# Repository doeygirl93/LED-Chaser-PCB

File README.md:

# Chiikawa LED chaser PCD
You can find my journals here: https://stasis.hackclub.com/dashboard/projects/cmnpnfhm200dn01pehbkvc9ek
---
## Description

This is a Blinky Board for stasis! Its very cool and when its powered it has a bunch of Leds "chasing" each other like after one turns on the one before it turns off and it goes through all the Led!

--- 
## Why I made It

I made it because this is one of my First Pcbs! I wanted something easy and people said to do this for the fundamentals. I wanted it to be useful so i made it chiikawa themed cause chiikawa makes me happy!

----
## Pictures

#### Pcb

### Schematic

## 3d Render 

## BOM

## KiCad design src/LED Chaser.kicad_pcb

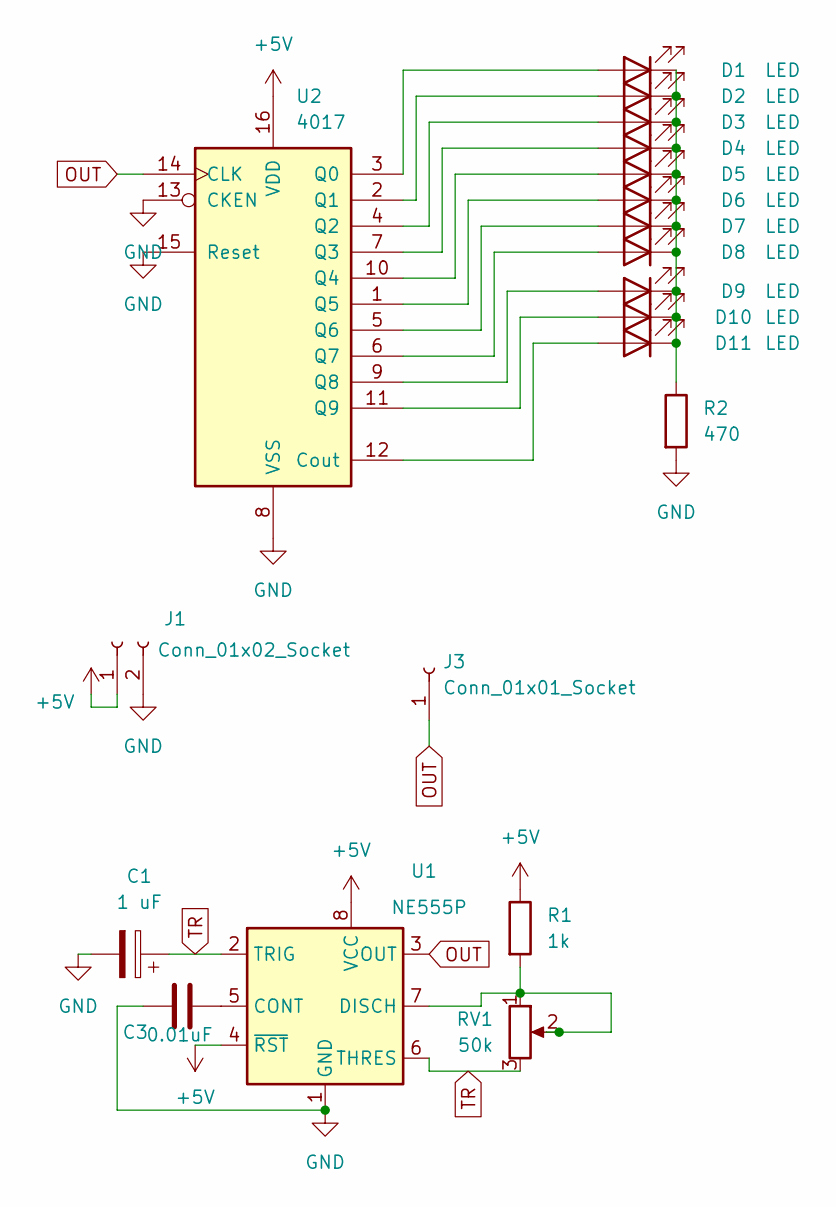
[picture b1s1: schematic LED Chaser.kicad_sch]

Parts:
C1: 1 uF; CP_Radial_D5.0mm_P2.00mm
C3: 0.01uF; CP_Radial_D5.0mm_P2.00mm
D1, D2, D3, D4, D5, D6, D7, D8, D9, D10, D11: LED; LED_D3.0mm
J1: Conn_01x02_Socket; PinHeader_1x02_P2.54mm_Vertical
J3: Conn_01x01_Socket; PinHeader_1x02_P2.54mm_Vertical
R1: 1k; R_Axial_DIN0207_L6.3mm_D2.5mm_P7.62mm_Horizontal
R2: 470; R_Axial_DIN0207_L6.3mm_D2.5mm_P7.62mm_Horizontal
RV1: 50k; Potentiometer_Vishay_T93YA_Vertical
U1: NE555P; DIP-8_W7.62mm
U2: 4017; N16

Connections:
+5V: J1.1, R1.1, U1.4 (~RST), U1.8 (VCC), U2.16 (VDD)
GND: C1.2, C3.1, J1.2, R2.2, U1.1 (GND), U2.8 (VSS), U2.13 (CKEN), U2.15 (Reset)
unnamed: D1.2 (A), U2.3 (Q0)
unnamed: D1.1 (K), D2.1 (K), D3.1 (K), D4.1 (K), D5.1 (K), D6.1 (K), D7.1 (K), D8.1 (K), D9.1 (K), D10.1 (K), D11.1 (K), R2.1
unnamed: D2.2 (A), U2.2 (Q1)
unnamed: D3.2 (A), U2.4 (Q2)
unnamed: D4.2 (A), U2.7 (Q3)
unnamed: D5.2 (A), U2.10 (Q4)
unnamed: D6.2 (A), U2.1 (Q5)
unnamed: D7.2 (A), U2.5 (Q6)
unnamed: D8.2 (A), U2.6 (Q7)
unnamed: D9.2 (A), U2.9 (Q8)
unnamed: D10.2 (A), U2.11 (Q9)
unnamed: D11.2 (A), U2.12 (Cout)
unnamed: C3.2, U1.5 (CONT)
unnamed: R1.2, RV1.1, RV1.2, U1.7 (DISCH)
OUT: J3.1 (Pin_1_1), U1.3 (OUT), U2.14 (CLK)
TR: C1.1, RV1.3, U1.2 (TRIG), U1.6 (THRES)

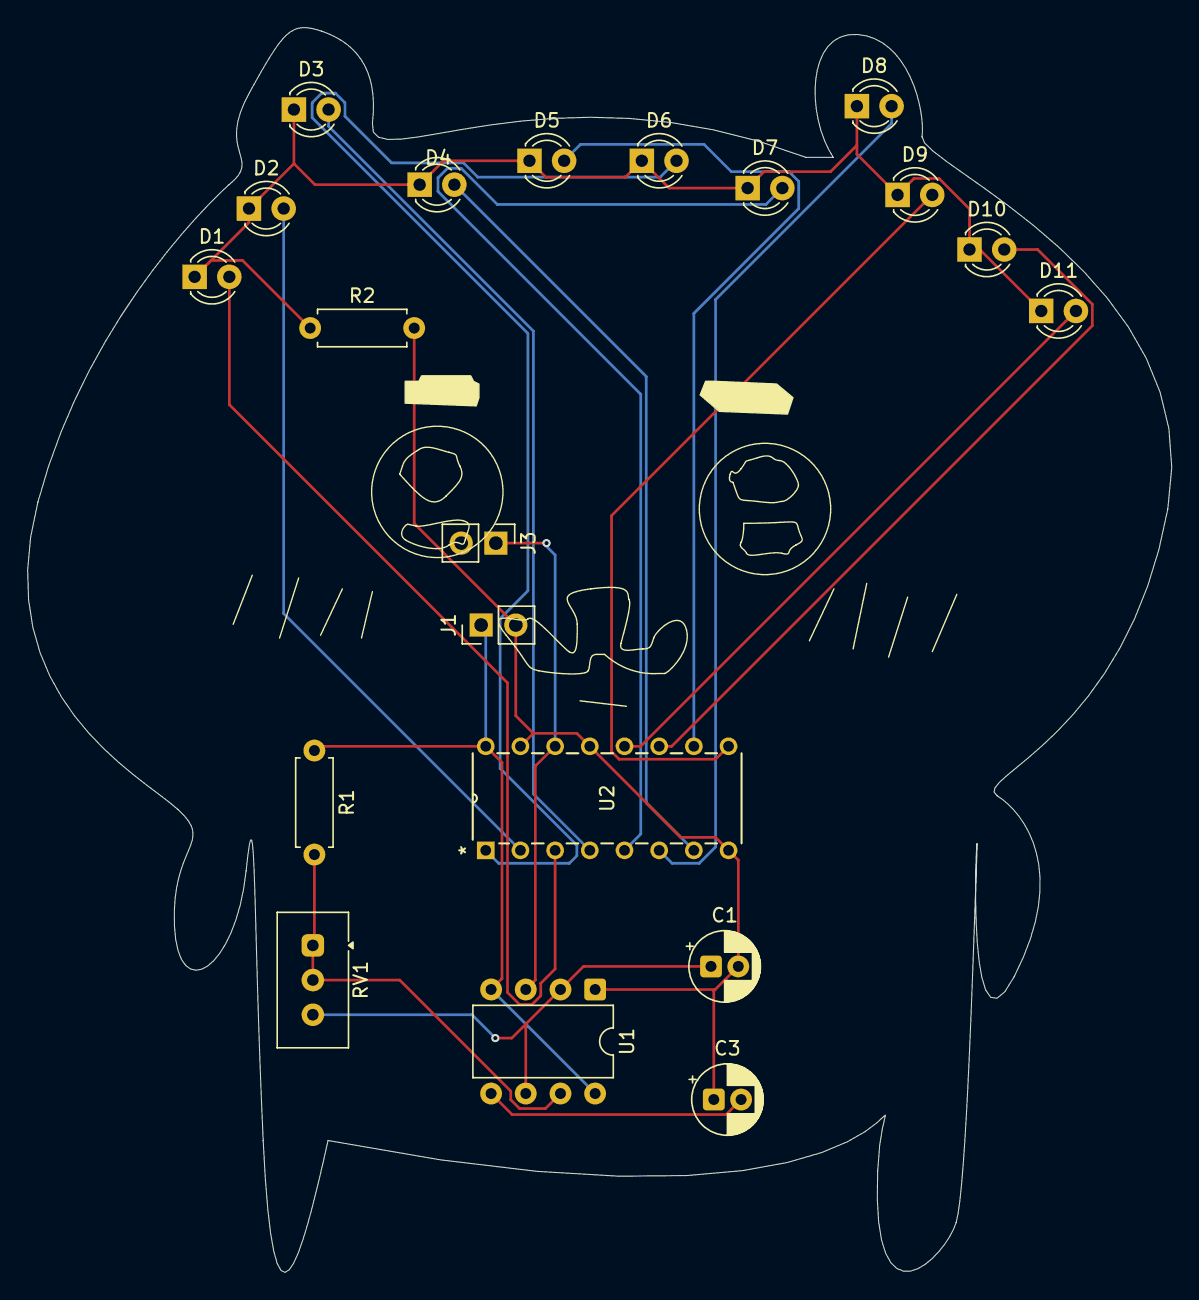
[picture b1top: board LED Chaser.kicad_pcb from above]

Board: 2 copper layers, 83.8 x 91.2 mm, 20 parts (0 on the bottom side), 18 nets.

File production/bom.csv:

Designator,Footprint,Quantity,Value,LCSC Part #
C1,CP_Radial_D5.0mm_P2.00mm,1,1 uF,
C3,CP_Radial_D5.0mm_P2.00mm,1,0.01uF,
"D1, D10, D11, D2, D3, D4, D5, D6, D7, D8, D9",LED_D3.0mm,11,LED,
J1,PinHeader_1x02_P2.54mm_Vertical,1,Conn_01x02_Socket,
J3,PinHeader_1x02_P2.54mm_Vertical,1,Conn_01x01_Socket,
R1,R_Axial_DIN0207_L6.3mm_D2.5mm_P7.62mm_Horizontal,1,1k,
R2,R_Axial_DIN0207_L6.3mm_D2.5mm_P7.62mm_Horizontal,1,470,
RV1,Potentiometer_Vishay_T93YA_Vertical,1,50k,
U1,DIP-8_W7.62mm,1,NE555P,
U2,N16,1,4017,

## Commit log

2026-04-13 Add main files
2026-04-13 Fix image links in README.md
    Updated image references in README with proper links.
2026-04-13 Remove BOM Part 2 image from README
2026-04-13 Add link to journals in README
    Added a link to personal journals in the README.
